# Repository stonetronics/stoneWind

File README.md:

# stoneWind

anemometer firmware for arduino uno based anemometer

This firmware and hardware enables an Arduino Uno to read the anemometer sensor found on https://www.thingiverse.com/thing:4216504
The Arduino shield (/hw) is drawn in Eagle 9.2.2, the Gerbers were generated for JLCPCB manufacturing
The Firmware (/src) is programmed in platformio

Features:
- 7 segment display
- sd card for logging and storage of lookup table
- ptc temperature sensor
- frequency counter
- schmitt trigger and signal conditioning/supply of the anemometer

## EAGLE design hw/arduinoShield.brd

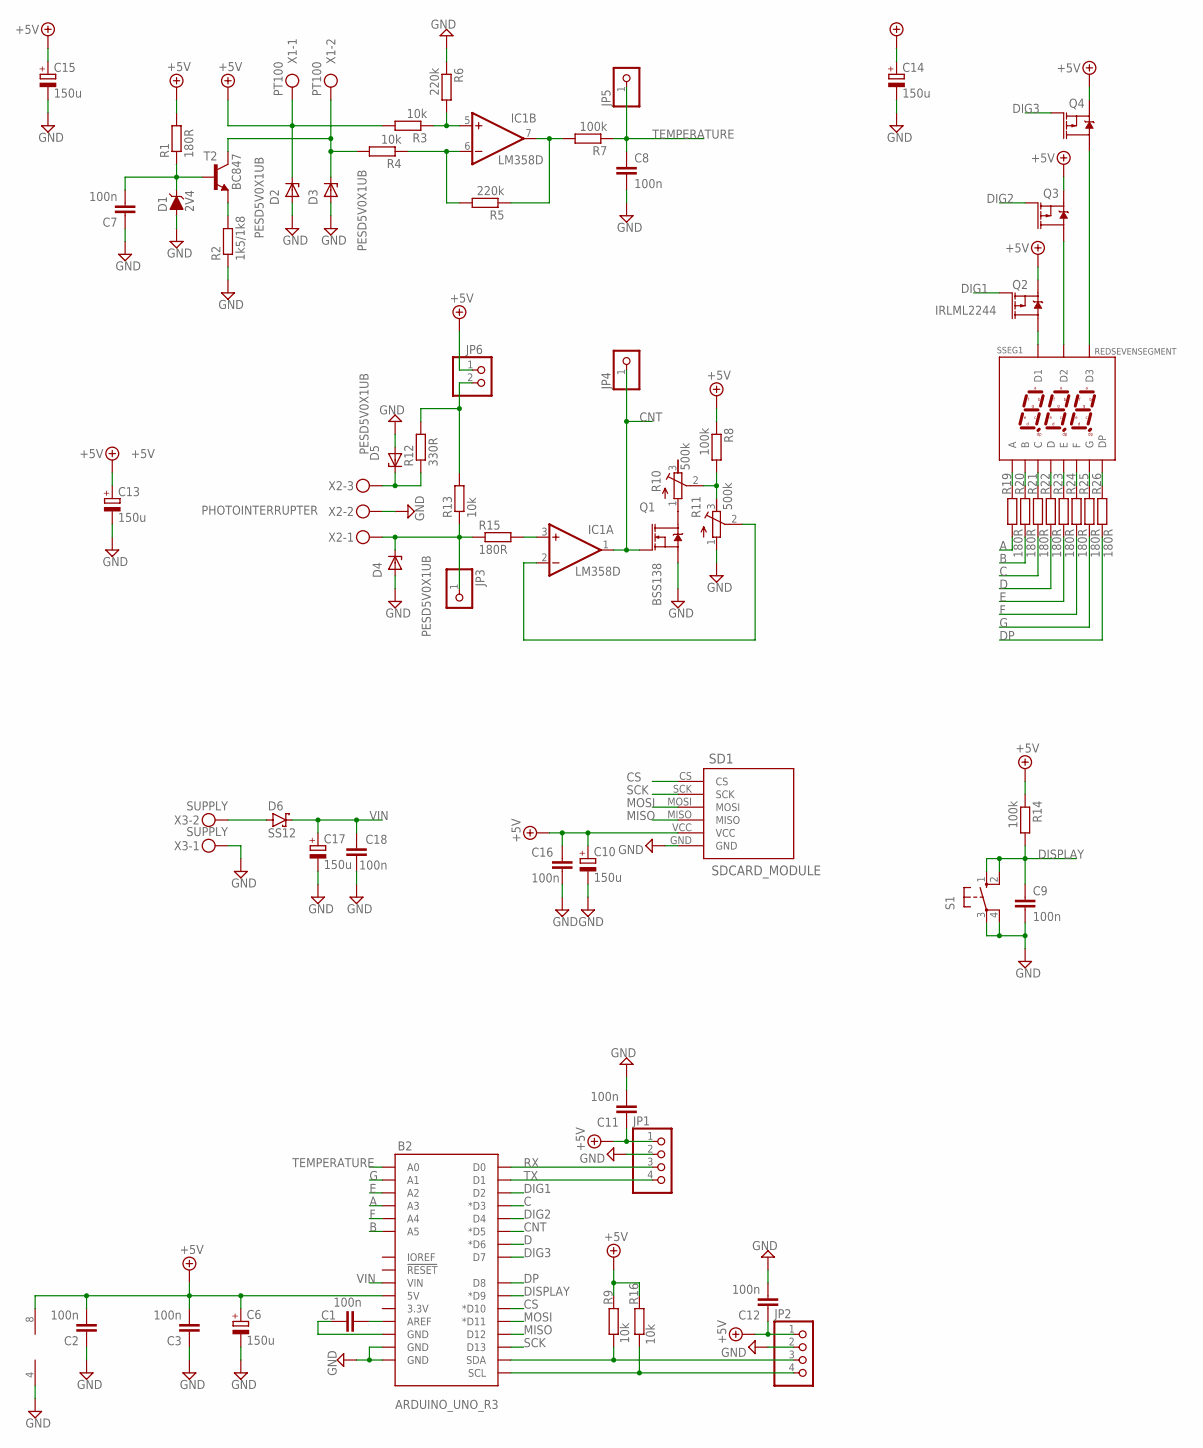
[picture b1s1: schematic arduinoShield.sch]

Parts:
B2: ARDUINO_UNO_R3; ARDUINO_R3_NOISP
C1, C2, C3, C7, C8, C9, C11, C12, C16, C18: 100n; C0805
C6, C10, C13, C14, C15, C17: 150u; D/7343-31R
D1: 2V4; SOD-323
D2, D3, D4, D5: PESD5V0X1UB; SOD523
D6: SS12; SMA
IC1: LM358D; SO08
JP1, JP2: PINHD-1X4; 1X04
JP3, JP4, JP5: PINHD-1X1; 1X01
JP6: PINHD-1X2; 1X02
Q1: BSS138; SOT23-3
Q2: IRLML2244; SOT23-3
Q3, Q4: 4.3A/20V/54mΩ; SOT23-3
R1, R15, R19, R20, R21, R22, R23, R24, R25, R26: 180R; R0805
R2: 1k5/1k8; R0805
R3, R4, R9, R13, R16: 10k; R0805
R5, R6: 220k; R0805
R7, R8, R14: 100k; R0805
R10, R11: 500k; RTRIM64Y
R12: 330R; R0805
S1: 10-XX; B3F-10XX
SD1: SDCARD_MODULE; SD_MODULE
SSEG1: REDSEVENSEGMENT
T2: BC847; SOT23-BEC
X1: PT100; 2_2.54MM
X2: PHOTOINTERRUPTER; MKDSN1,5/3-5,08
X3: SUPPLY; MKDSN1,5/2-5,08

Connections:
+5V: B2.5V, C2.2, C3.2, C6.+, C10.+, C11.1, C12.1, C13.+, C14.+, C15.+, C16.1, D2.1 (K), IC1.8 (V+), JP1.1, JP2.1, JP6.1, Q2.2 (S), Q3.2 (S), Q4.2 (S), R1.2, R3.2, R8.1, R9.2, R14.1, R16.2, SD1.VCC, X1.1
A: B2.A3, R19.1
B: B2.A5, R20.1
C: B2.D3 (*D3), R21.1
CNT: B2.D5 (*D5), IC1.1 (OUT), JP4.1, Q1.1 (G)
CS: B2.D10 (*D10), SD1.CS
D: B2.D6 (*D6), R22.1
DIG1: B2.D2, Q2.1 (G)
DIG2: B2.D4, Q3.1 (G)
DIG3: B2.D7, Q4.1 (G)
DISPLAY: B2.D9 (*D9), C9.1, R14.2, S1.1 (S), S1.2 (S1)
DP: B2.D8, R26.1
E: B2.A2, R23.1
F: B2.A4, R24.1
G: B2.A1, R25.1
GND: B2.GND@1 (GND), B2.GND@2 (GND), C2.1, C3.1, C6.-, C7.1, C8.2, C9.2, C10.-, C11.2, C12.2, C13.-, C14.-, C15.-, C16.2, C17.-, C18.1, D1.A, D2.2 (A), D3.2 (A), D4.2 (A), D5.2 (A), IC1.4 (V-), JP1.2, JP2.2, Q1.2 (S), R2.1, R6.1, R11.1 (A), S1.3, S1.4 (P1), SD1.GND, X2.2, X3.1
MISO: B2.D12, SD1.MISO
MOSI: B2.D11 (*D11), SD1.MOSI
unnamed: B2.AREF, C1.2
unnamed: C7.2, D1.C, R1.1, T2.B
unnamed: R2.2, T2.E
unnamed: D3.1 (K), R4.2, T2.C, X1.2
unnamed: IC1.5 (+IN), R3.1, R6.2
unnamed: IC1.6 (-IN), R4.1, R5.2
unnamed: IC1.7 (OUT), R5.1, R7.2
unnamed: D5.1 (K), R12.1, X2.3
unnamed: B2.SDA, JP2.3, R9.1
unnamed: Q1.3 (D), R10.1 (A)
unnamed: R8.2, R10.2 (S), R11.3 (E)
unnamed: IC1.2 (-IN), R11.2 (S)
unnamed: D4.1 (K), JP3.1, R13.1, R15.1, X2.1
unnamed: B2.SCL, JP2.4, R16.1
unnamed: JP6.2, R12.2, R13.2
unnamed: B2.GND@3 (GND), C1.1
unnamed: Q2.3 (D), SSEG1.2 (D1)
unnamed: Q3.3 (D), SSEG1.4 (D2)
unnamed: Q4.3 (D), SSEG1.5 (D3)
unnamed: D6.A, X3.2
unnamed: R19.2, SSEG1.9 (A)
unnamed: R20.2, SSEG1.7 (B)
unnamed: R21.2, SSEG1.1 (C)
unnamed: R22.2, SSEG1.3 (D)
unnamed: R23.2, SSEG1.10 (E)
unnamed: R24.2, SSEG1.8 (F)
unnamed: R25.2, SSEG1.11 (G)
unnamed: R26.2, SSEG1.6 (DP)
unnamed: IC1.3 (+IN), R15.2
RX: B2.D0, JP1.3
SCK: B2.D13, SD1.SCK
TEMPERATURE: B2.A0, C8.1, JP5.1, R7.1
TX: B2.D1, JP1.4
VIN: B2.VIN, C17.+, C18.2, D6.C

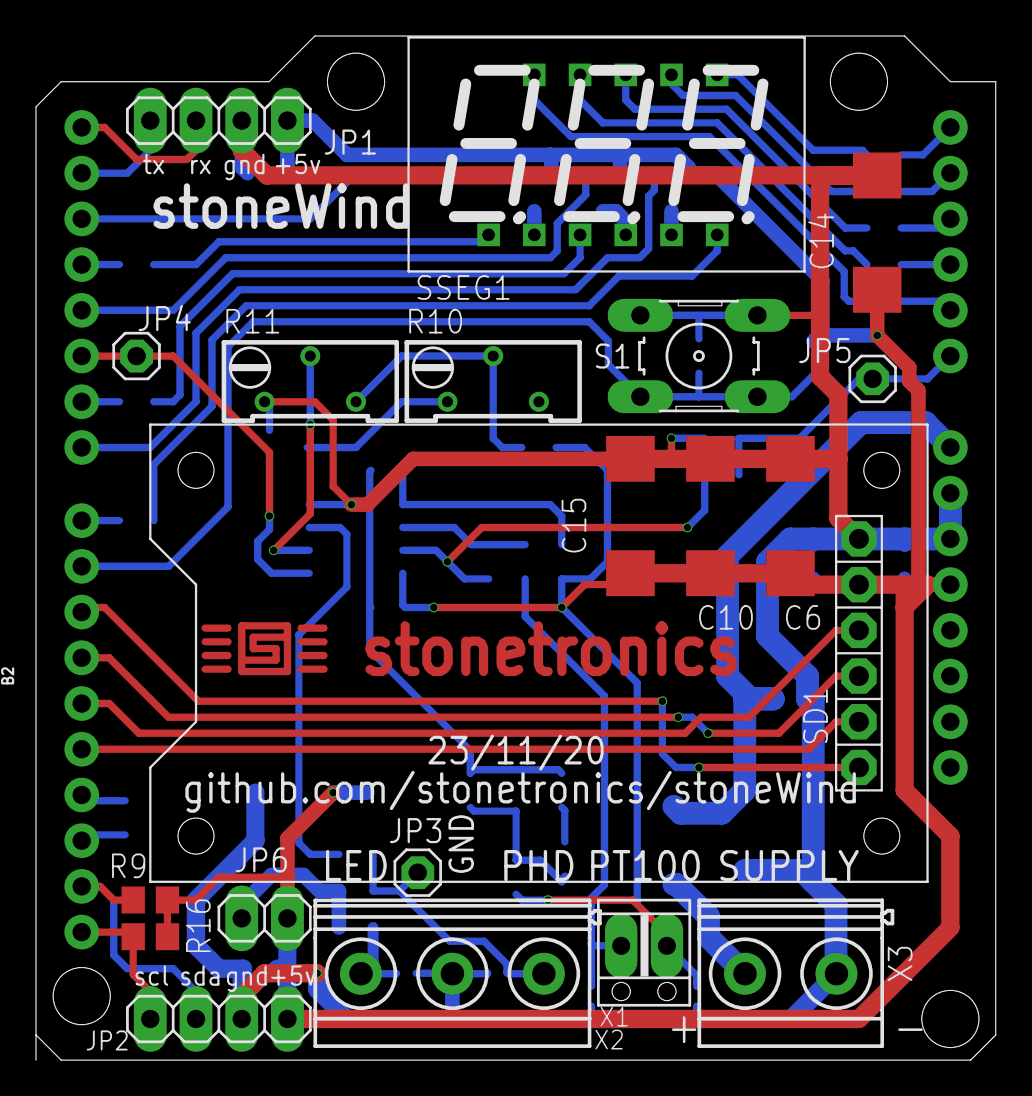
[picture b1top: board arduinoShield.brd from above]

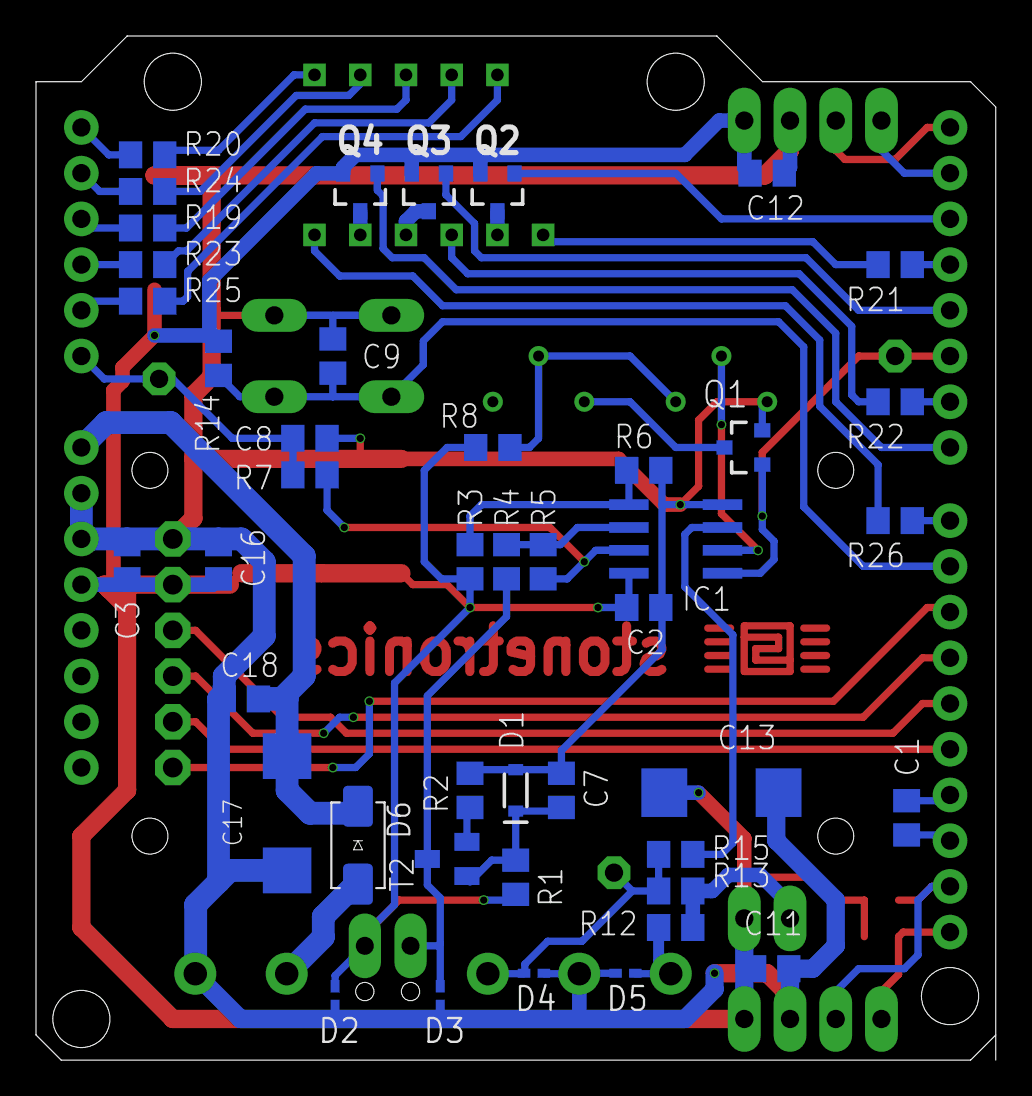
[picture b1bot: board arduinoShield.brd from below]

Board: 2 copper layers, 53.3 x 56.9 mm, 65 parts (44 on the bottom side), 52 nets.

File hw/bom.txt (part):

Stückliste exportiert aus /home/stone/GIT/stoneWind/hw/arduinoShield.sch am 18.09.20 22:02

Qty Value            Device                     Package          Parts                                           Description                                                                              CREATED_BY    DIGIKEY_PART_NUMBER MANUFACTURER     MF MPN      OC_FARNELL OC_NEWARK PACKAGE        PROD_ID     SPICEMODEL SPICEPREFIX SPICEPREFIXL VALUE         
1                    10-XX                      B3F-10XX         S1                                              OMRON SWITCH                                                                                                                                   B3F-1000 176432     36M3542                                                                                
3                    PINHD-1X1                  1X01             JP3, JP4, JP5                                   PIN HEADER                                                                                                                                                                                                                                                
1                    PINHD-1X2                  1X02             JP6                                             PIN HEADER                                                                                                                                                                                                                                                
2                    PINHD-1X4                  1X04             JP1, JP2                                        PIN HEADER                                                                                                                                                                                                                                                
3   100k             R-EU_R0805                 R0805            R7, R8, R14                                     RESISTOR, European symbol                                                                                                                                                                                          R                                      
10  100n             C-EUC0805                  C0805            C1, C2, C3, C7, C8, C9, C11, C12, C16, C18      CAPACITOR, European symbol                                                                                                                                                                                         C                                      
5   10k              R-EU_R0805                 R0805            R3, R4, R9, R13, R16                            RESISTOR, European symbol                                                                                                                                                                                          R                                      
6   150u             CPOL-EUD/7343-31R          D/7343-31R       C6, C10, C13, C14, C15, C17                     POLARIZED CAPACITOR, European symbol                                                                                                                                                                               C                                      
10  180R             R-EU_R0805                 R0805            R1, R15, R19, R20, R21, R22, R23, R24, R25, R26 RESISTOR, European symbol                                                                                                                                                                                          R                                      
1   1k5/1k8          R-EU_R0805                 R0805            R2                                              RESISTOR, European symbol                                                                                                                                                                                          R                                      
2   220k             R-EU_R0805                 R0805            R5, R6                                          RESISTOR, European symbol                                                                                                                                                                                          R                                      
1   2V4              DIODE-ZENER-BZT52C3V6S     SOD-323          D1                                              Zener Diode                                                                                                                                                                                 DIO-08199                                       3.6V          
1   330R             R-EU_R0805                 R0805            R12                                             RESISTOR, European symbol                                                                                                                                                                                          R                                      
2   4.3A/20V/54mΩ    MOSFET_PCH-IRLML2244       SOT23-3          Q3, Q4                                          P-channel MOSFETs                                                                                                                                                                           TRANS-11153                                     4.3A/20V/54mΩ 
2   500k             R-TRIMM64Y                 RTRIM64Y         R10, R11                                        Trimm resistor                                                                                                                                                                                          X                      POT                        
1   ARDUINO_UNO_R3   ARDUINO_UNO_R3_HOLES_NOISP ARDUINO_R3_NOISP B2                                                                                                                                                                                                                                                                                                        
1   BC847            BC847-NPN-SOT23-BEC        SOT23-BEC        T2                                              NPN Transistror                                                                                                                                                                                                                                           
1   BSS138           MOSFET-NCH-BSS138          SOT23-3          Q1                                              N-channel MOSFETs                                                                                                                                                                           TRANS-00830                                     220mA/50V/3.5Ω
1   IRLML2244        MOSFET_PCH-IRLML2244       SOT23-3          Q2                                              P-channel MOSFETs                                                                                                                                                                           TRANS-11153                                     4.3A/20V/54mΩ 
1   LM358D           LM358D                     SO08             IC1                                             OP AMP also LM158; LM258; LM2904                                                                                                                                                                                                                          
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
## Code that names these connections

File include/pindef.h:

#ifndef __pindef_h__
#define __pindef_h__

#define PIN_TEMPERATURE   14
#define PIN_G             15
#define PIN_E             16
#define PIN_A             17
#define PIN_F             18
#define PIN_B             19
#define PIN_RX            0
#define PIN_TX            1
#define PIN_DIG1          2
#define PIN_C             3
#define PIN_DIG2          4
#define PIN_CNT           5
#define PIN_D             6
#define PIN_DIG3          7
#define PIN_DP            8
#define PIN_DISPLAY       9
#define PIN_CS            10
#define PIN_MOSI          11
#define PIN_MISO          12
#define PIN_SCK           13

#endif

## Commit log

2020-11-03 First PCB design
2020-11-05 add seven segment driver and frequency counting for measuring wind speed
2020-11-05 add Lookup Table and millis() handling, update readme
2020-11-13 transform LUT from static to class, LUT loading from sd card file csv data log to sd card
2020-11-19 add pdf schematic

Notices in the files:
parts and their libraries:
SparkFun-DiscreteSemi: Licensing: Creative Commons ShareAlike 4.0 International - https://creativecommons.org/licenses/by-sa/4.0
